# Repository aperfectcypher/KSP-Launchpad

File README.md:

# KSP-Launchpad
## THIS IS AN EARLY WORK IN PROGRESS

Firmware for the KSP-Launchpad board.

MCU is an ATmega2560.
## Features

* Dual 3-axis joystick for rotation and translation
* Linear potentiometers for throttle
* SAS LED
* RCS LED
* LED bars as ship ressources gauges
* LCD screen (128x32px) for ship status

## Schematics

The schematics are written using kicad.
The schematics are available in the `schematics` directory.

## License

The firmware and schematics are licensed under the Unlicense license.

## Author

[Aperfectcypher](https://github.com/aperfectcypher)

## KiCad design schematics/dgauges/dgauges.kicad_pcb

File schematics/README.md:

# Schematics
The schematics are written using kicad.

Required libraries:
* [Connectors_JST](https://github.com/KiCad/Connectors_JST.pretty)

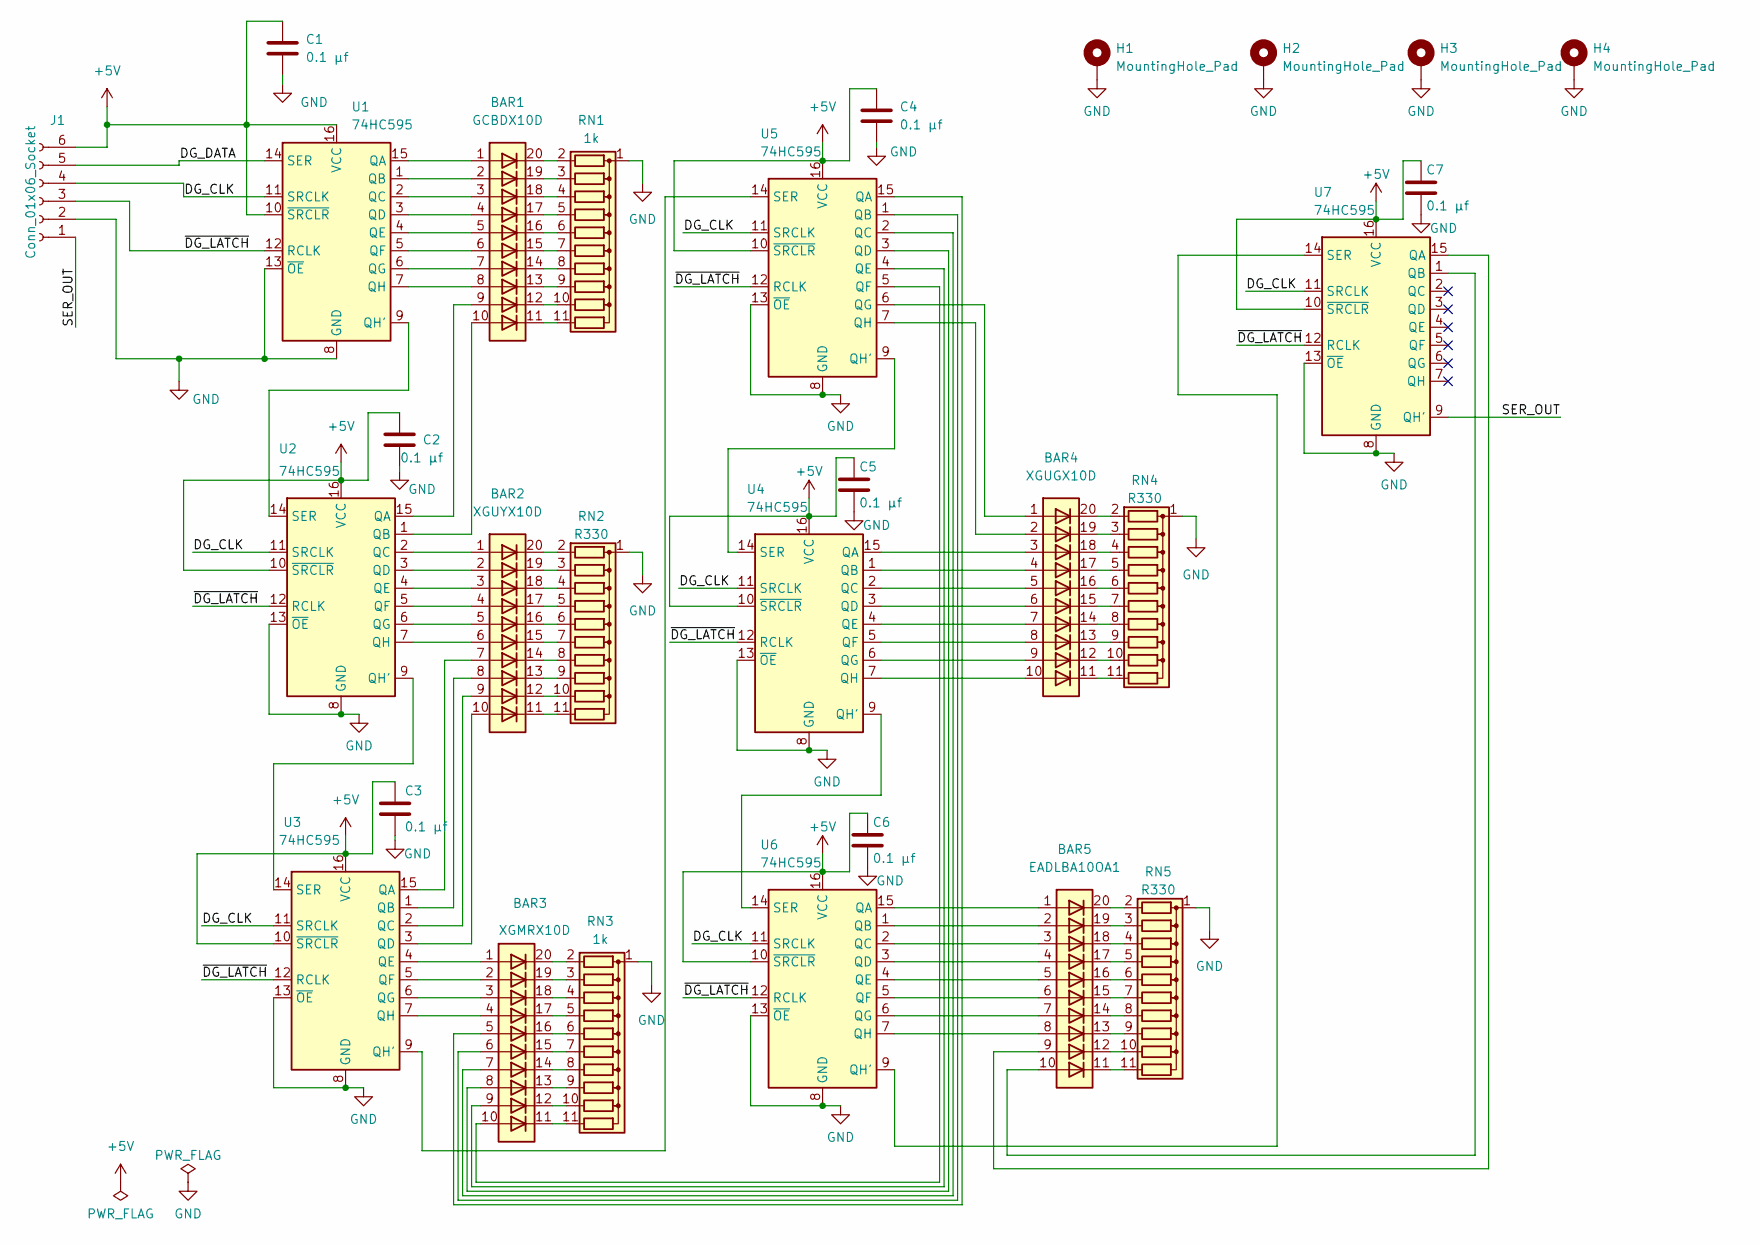
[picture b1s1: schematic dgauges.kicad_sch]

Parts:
BAR1: GCBDX10D; HDSP-4832
BAR2: XGUYX10D; HDSP-4832
BAR3: XGMRX10D; HDSP-4832
BAR4: XGUGX10D; HDSP-4832
BAR5: EADLBA10OA1; HDSP-4832
C1, C2, C3, C4, C5, C6, C7: 0.1 µf; C_Disc_D4.3mm_W1.9mm_P5.00mm; LCSC C254085
H1, H2, H3, H4: MountingHole_Pad; MountingHole_2.2mm_M2_ISO7380_Pad
J1: Conn_01x06_Socket; JST_PH_B6B-PH-K_1x06_P2.00mm_Vertical
RN1, RN3: 1k; R_Array_SIP11; digikey 4611X-101-102LF-ND
RN2, RN4, RN5: R330; R_Array_SIP11; digi-key 4611X-101-331LF
U1, U2, U3, U4, U5, U6, U7: 74HC595; DIP-16_W7.62mm

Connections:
+5V: C1.1, C2.1, C3.1, C4.1, C5.1, C6.1, C7.1, J1.6, U1.10 (~SRCLR), U1.16 (VCC), U2.10 (~SRCLR), U2.16 (VCC), U3.10 (~SRCLR), U3.16 (VCC), U4.10 (~SRCLR), U4.16 (VCC), U5.10 (~SRCLR), U5.16 (VCC), U6.10 (~SRCLR), U6.16 (VCC), U7.10 (~SRCLR), U7.16 (VCC)
/DG_CLK: J1.4, U1.11 (SRCLK), U2.11 (SRCLK), U3.11 (SRCLK), U4.11 (SRCLK), U5.11 (SRCLK), U6.11 (SRCLK), U7.11 (SRCLK)
/DG_DATA: J1.5, U1.14 (SER)
/SER_OUT: J1.1, U7.9 (QH')
/~DG_LATCH: J1.3, U1.12 (RCLK), U2.12 (RCLK), U3.12 (RCLK), U4.12 (RCLK), U5.12 (RCLK), U6.12 (RCLK), U7.12 (RCLK)
GND: C1.2, C2.2, C3.2, C4.2, C5.2, C6.2, C7.2, H1.1, H2.1, H3.1, H4.1, J1.2, RN1.1 (common), RN2.1 (common), RN3.1 (common), RN4.1 (common), RN5.1 (common), U1.8 (GND), U1.13 (~OE), U2.8 (GND), U2.13 (~OE), U3.8 (GND), U3.13 (~OE), U4.8 (GND), U4.13 (~OE), U5.8 (GND), U5.13 (~OE), U6.8 (GND), U6.13 (~OE), U7.8 (GND), U7.13 (~OE)
unnamed: BAR1.20 (K), RN1.2 (R1)
unnamed: BAR1.19 (K), RN1.3 (R2)
unnamed: BAR1.18 (K), RN1.4 (R3)
unnamed: BAR1.17 (K), RN1.5 (R4)
unnamed: BAR1.16 (K), RN1.6 (R5)
unnamed: BAR1.15 (K), RN1.7 (R6)
unnamed: BAR1.14 (K), RN1.8 (R7)
unnamed: BAR1.13 (K), RN1.9 (R8)
unnamed: BAR1.12 (K), RN1.10 (R9)
unnamed: BAR1.11 (K), RN1.11 (R10)
unnamed: BAR2.20 (K), RN2.2 (R1)
unnamed: BAR2.19 (K), RN2.3 (R2)
unnamed: BAR2.18 (K), RN2.4 (R3)
unnamed: BAR2.17 (K), RN2.5 (R4)
unnamed: BAR2.16 (K), RN2.6 (R5)
unnamed: BAR2.15 (K), RN2.7 (R6)
unnamed: BAR2.14 (K), RN2.8 (R7)
unnamed: BAR2.13 (K), RN2.9 (R8)
unnamed: BAR2.12 (K), RN2.10 (R9)
unnamed: BAR2.11 (K), RN2.11 (R10)
unnamed: BAR3.20 (K), RN3.2 (R1)
unnamed: BAR3.19 (K), RN3.3 (R2)
unnamed: BAR3.18 (K), RN3.4 (R3)
unnamed: BAR3.17 (K), RN3.5 (R4)
unnamed: BAR3.16 (K), RN3.6 (R5)
unnamed: BAR3.15 (K), RN3.7 (R6)
unnamed: BAR3.14 (K), RN3.8 (R7)
unnamed: BAR3.13 (K), RN3.9 (R8)
unnamed: BAR3.12 (K), RN3.10 (R9)
unnamed: BAR3.11 (K), RN3.11 (R10)
unnamed: BAR4.20 (K), RN4.2 (R1)
unnamed: BAR4.19 (K), RN4.3 (R2)
unnamed: BAR4.18 (K), RN4.4 (R3)
unnamed: BAR4.17 (K), RN4.5 (R4)
unnamed: BAR4.16 (K), RN4.6 (R5)
unnamed: BAR4.15 (K), RN4.7 (R6)
unnamed: BAR4.14 (K), RN4.8 (R7)
unnamed: BAR4.13 (K), RN4.9 (R8)
unnamed: BAR4.12 (K), RN4.10 (R9)
unnamed: BAR4.11 (K), RN4.11 (R10)
unnamed: BAR5.20 (K), RN5.2 (R1)
unnamed: BAR5.19 (K), RN5.3 (R2)
unnamed: BAR5.18 (K), RN5.4 (R3)
unnamed: BAR5.17 (K), RN5.5 (R4)
unnamed: BAR5.16 (K), RN5.6 (R5)
unnamed: BAR5.15 (K), RN5.7 (R6)
unnamed: BAR5.14 (K), RN5.8 (R7)
unnamed: BAR5.13 (K), RN5.9 (R8)
unnamed: BAR5.12 (K), RN5.10 (R9)
unnamed: BAR5.11 (K), RN5.11 (R10)
unnamed: BAR1.1 (A), U1.15 (QA)
unnamed: BAR1.2 (A), U1.1 (QB)
unnamed: BAR1.3 (A), U1.2 (QC)
unnamed: BAR1.4 (A), U1.3 (QD)
unnamed: BAR1.5 (A), U1.4 (QE)
unnamed: BAR1.6 (A), U1.5 (QF)
unnamed: BAR1.7 (A), U1.6 (QG)
unnamed: U1.9 (QH'), U2.14 (SER)
unnamed: BAR1.8 (A), U1.7 (QH)
unnamed: BAR1.9 (A), U2.15 (QA)
unnamed: BAR1.10 (A), U2.1 (QB)
unnamed: BAR2.1 (A), U2.2 (QC)
unnamed: BAR2.2 (A), U2.3 (QD)
unnamed: BAR2.3 (A), U2.4 (QE)
unnamed: BAR2.4 (A), U2.5 (QF)
unnamed: BAR2.5 (A), U2.6 (QG)
unnamed: U2.9 (QH'), U3.14 (SER)
unnamed: BAR2.6 (A), U2.7 (QH)
unnamed: BAR2.7 (A), U3.15 (QA)
unnamed: BAR2.8 (A), U3.1 (QB)
unnamed: BAR2.9 (A), U3.2 (QC)
unnamed: BAR2.10 (A), U3.3 (QD)
unnamed: BAR3.1 (A), U3.4 (QE)
unnamed: BAR3.2 (A), U3.5 (QF)
unnamed: BAR3.3 (A), U3.6 (QG)
unnamed: U3.9 (QH'), U5.14 (SER)
unnamed: BAR3.4 (A), U3.7 (QH)
unnamed: BAR4.3 (A), U4.15 (QA)
unnamed: BAR4.4 (A), U4.1 (QB)
unnamed: BAR4.5 (A), U4.2 (QC)
unnamed: BAR4.6 (A), U4.3 (QD)
unnamed: BAR4.7 (A), U4.4 (QE)
unnamed: BAR4.8 (A), U4.5 (QF)
unnamed: BAR4.9 (A), U4.6 (QG)
unnamed: U4.9 (QH'), U6.14 (SER)
unnamed: BAR4.10 (A), U4.7 (QH)
unnamed: U4.14 (SER), U5.9 (QH')
unnamed: BAR3.5 (A), U5.15 (QA)
unnamed: BAR3.6 (A), U5.1 (QB)
unnamed: BAR3.7 (A), U5.2 (QC)
unnamed: BAR3.8 (A), U5.3 (QD)
unnamed: BAR3.9 (A), U5.4 (QE)
unnamed: BAR3.10 (A), U5.5 (QF)
unnamed: BAR4.1 (A), U5.6 (QG)
unnamed: BAR4.2 (A), U5.7 (QH)
unnamed: BAR5.1 (A), U6.15 (QA)
unnamed: BAR5.2 (A), U6.1 (QB)
unnamed: BAR5.3 (A), U6.2 (QC)
unnamed: BAR5.4 (A), U6.3 (QD)
unnamed: BAR5.5 (A), U6.4 (QE)
unnamed: BAR5.6 (A), U6.5 (QF)
unnamed: BAR5.7 (A), U6.6 (QG)
unnamed: U6.9 (QH'), U7.14 (SER)
unnamed: BAR5.8 (A), U6.7 (QH)
unnamed: BAR5.9 (A), U7.15 (QA)
unnamed: BAR5.10 (A), U7.1 (QB)

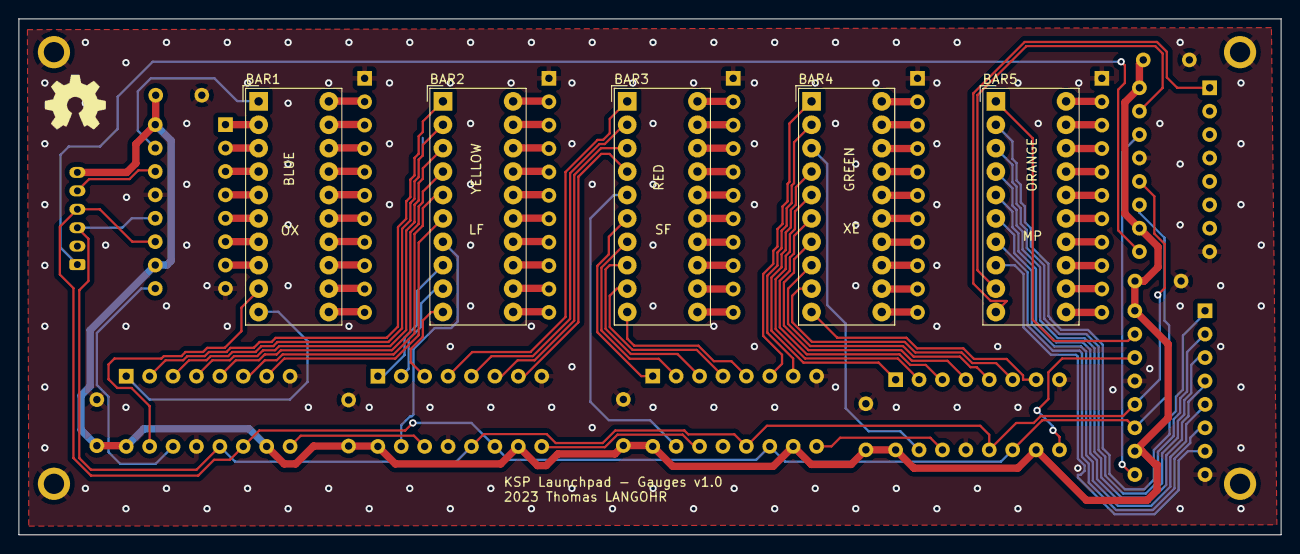
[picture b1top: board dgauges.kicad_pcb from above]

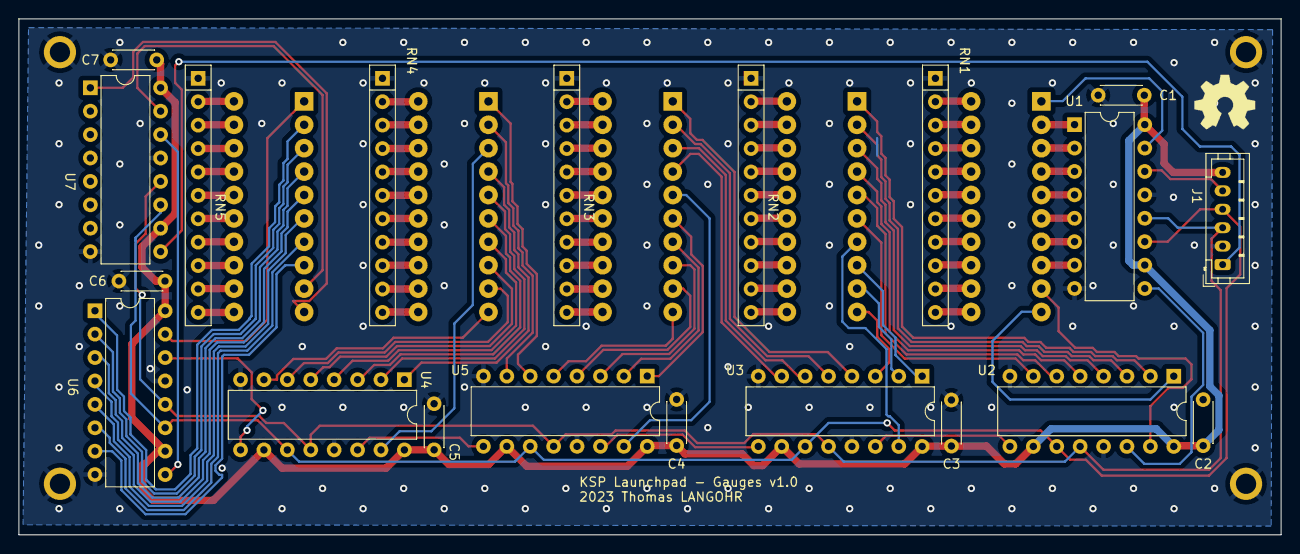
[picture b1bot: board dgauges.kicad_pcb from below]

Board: 2 copper layers, 137.0 x 56.0 mm, 29 parts (20 on the bottom side), 112 nets.

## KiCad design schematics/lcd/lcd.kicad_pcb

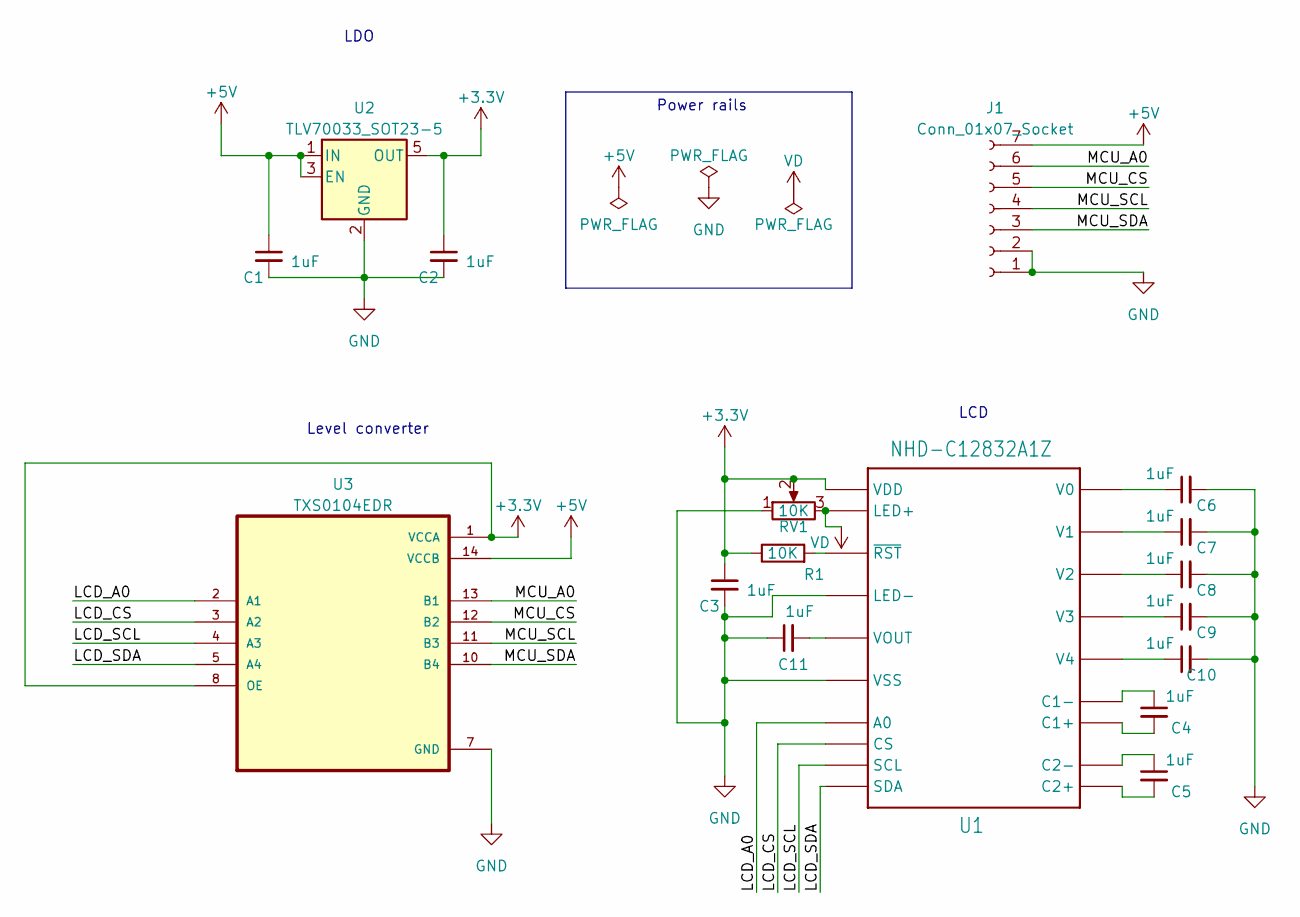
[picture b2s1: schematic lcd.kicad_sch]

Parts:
C1, C2, C3, C4, C5, C6, C7, C8, C9, C10, C11: 1uF; C_0603_1608Metric; lcsc C59302
J1: Conn_01x07_Socket; JST_PH_B7B-PH-K_1x07_P2.00mm_Vertical
R1: 10K; R_0603_1608Metric; lcsc C25804
RV1: 10K; Potentiometer_Bourns_3314G_Vertical; lcsc C780220
U1: NHD-C12832A1Z; JLCPCB BOM 0
U2: TLV70033_SOT23-5; SOT-23-5
U3: TXS0104EDR; SOIC127P600X175-14N; LCSC C79342

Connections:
+3.3V: C2.1, C3.1, R1.1, RV1.2, U1.P12 (VDD), U2.5 (OUT), U3.1 (VCCA), U3.8 (OE)
+5V: C1.1, J1.7, U2.1 (IN), U2.3 (EN), U3.14 (VCCB)
/LCD_A0: U1.P15 (A0), U3.2 (A1)
/LCD_CS: U1.P17 (CS), U3.3 (A2)
/LCD_SCL: U1.P14 (SCL), U3.4 (A3)
/LCD_SDA: U1.P13 (SDA), U3.5 (A4)
/MCU_A0: J1.6, U3.13 (B1)
/MCU_CS: J1.5, U3.12 (B2)
/MCU_SCL: J1.4, U3.11 (B3)
/MCU_SDA: J1.3, U3.10 (B4)
GND: C1.2, C2.2, C3.2, C6.2, C7.2, C8.2, C9.2, C10.2, C11.1, J1.1, J1.2, RV1.1, U1.P11 (VSS), U1.P19 (LED-), U2.2 (GND), U3.7 (GND)
unnamed: C4.2, U1.P8 (C1+)
unnamed: C4.1, U1.P9 (C1-)
unnamed: C5.2, U1.P7 (C2+)
unnamed: C5.1, U1.P6 (C2-)
unnamed: C6.1, U1.P1 (V0)
unnamed: C7.1, U1.P2 (V1)
unnamed: C8.1, U1.P3 (V2)
unnamed: C9.1, U1.P4 (V3)
unnamed: C10.1, U1.P5 (V4)
unnamed: C11.2, U1.P10 (VOUT)
unnamed: R1.2, U1.P16 (~RST)
VD: RV1.3, U1.P18 (LED+)

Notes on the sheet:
LCD
Level converter
Power rails
LDO

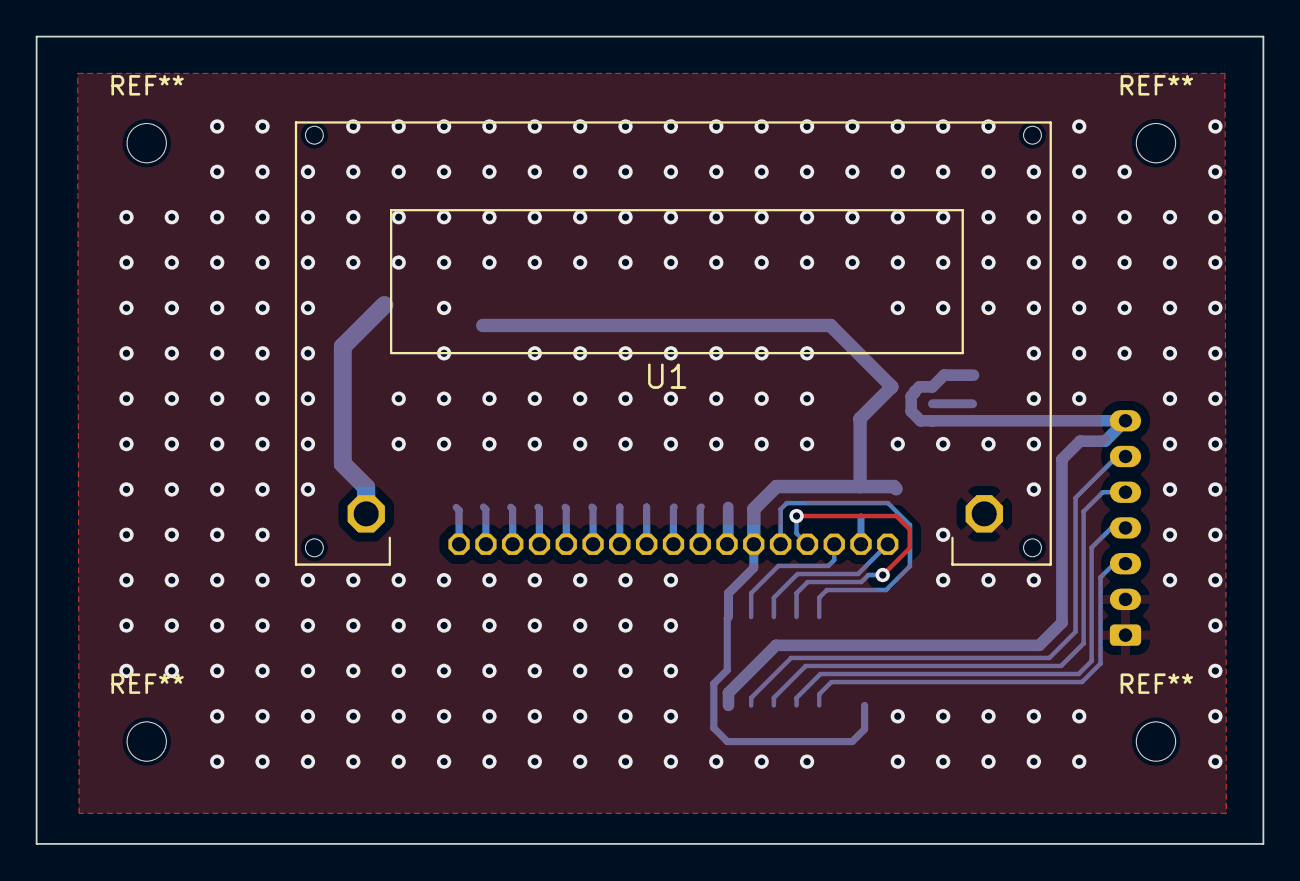
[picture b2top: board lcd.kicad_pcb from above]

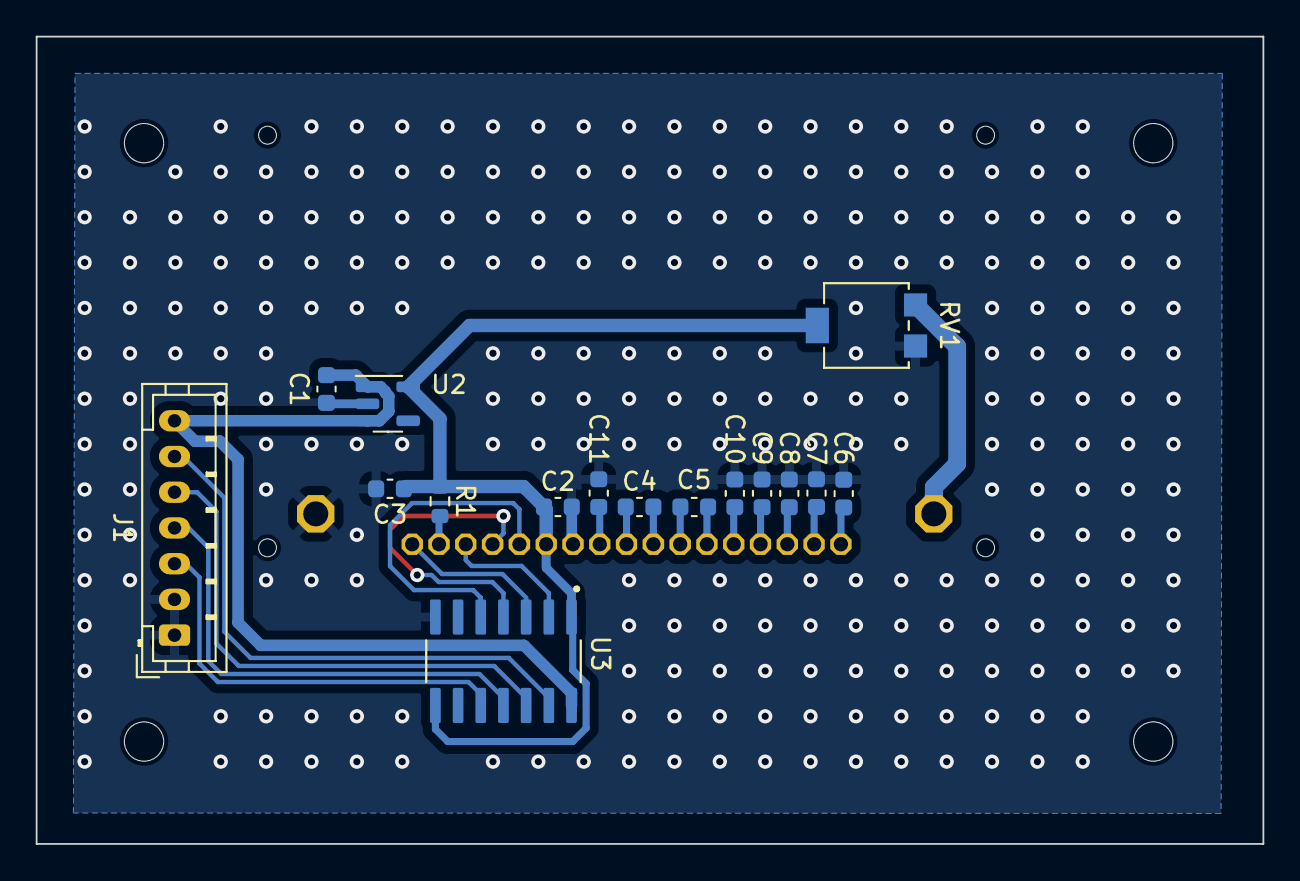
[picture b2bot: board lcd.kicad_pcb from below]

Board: 2 copper layers, 68.7 x 45.2 mm, 17 parts (16 on the bottom side), 23 nets.

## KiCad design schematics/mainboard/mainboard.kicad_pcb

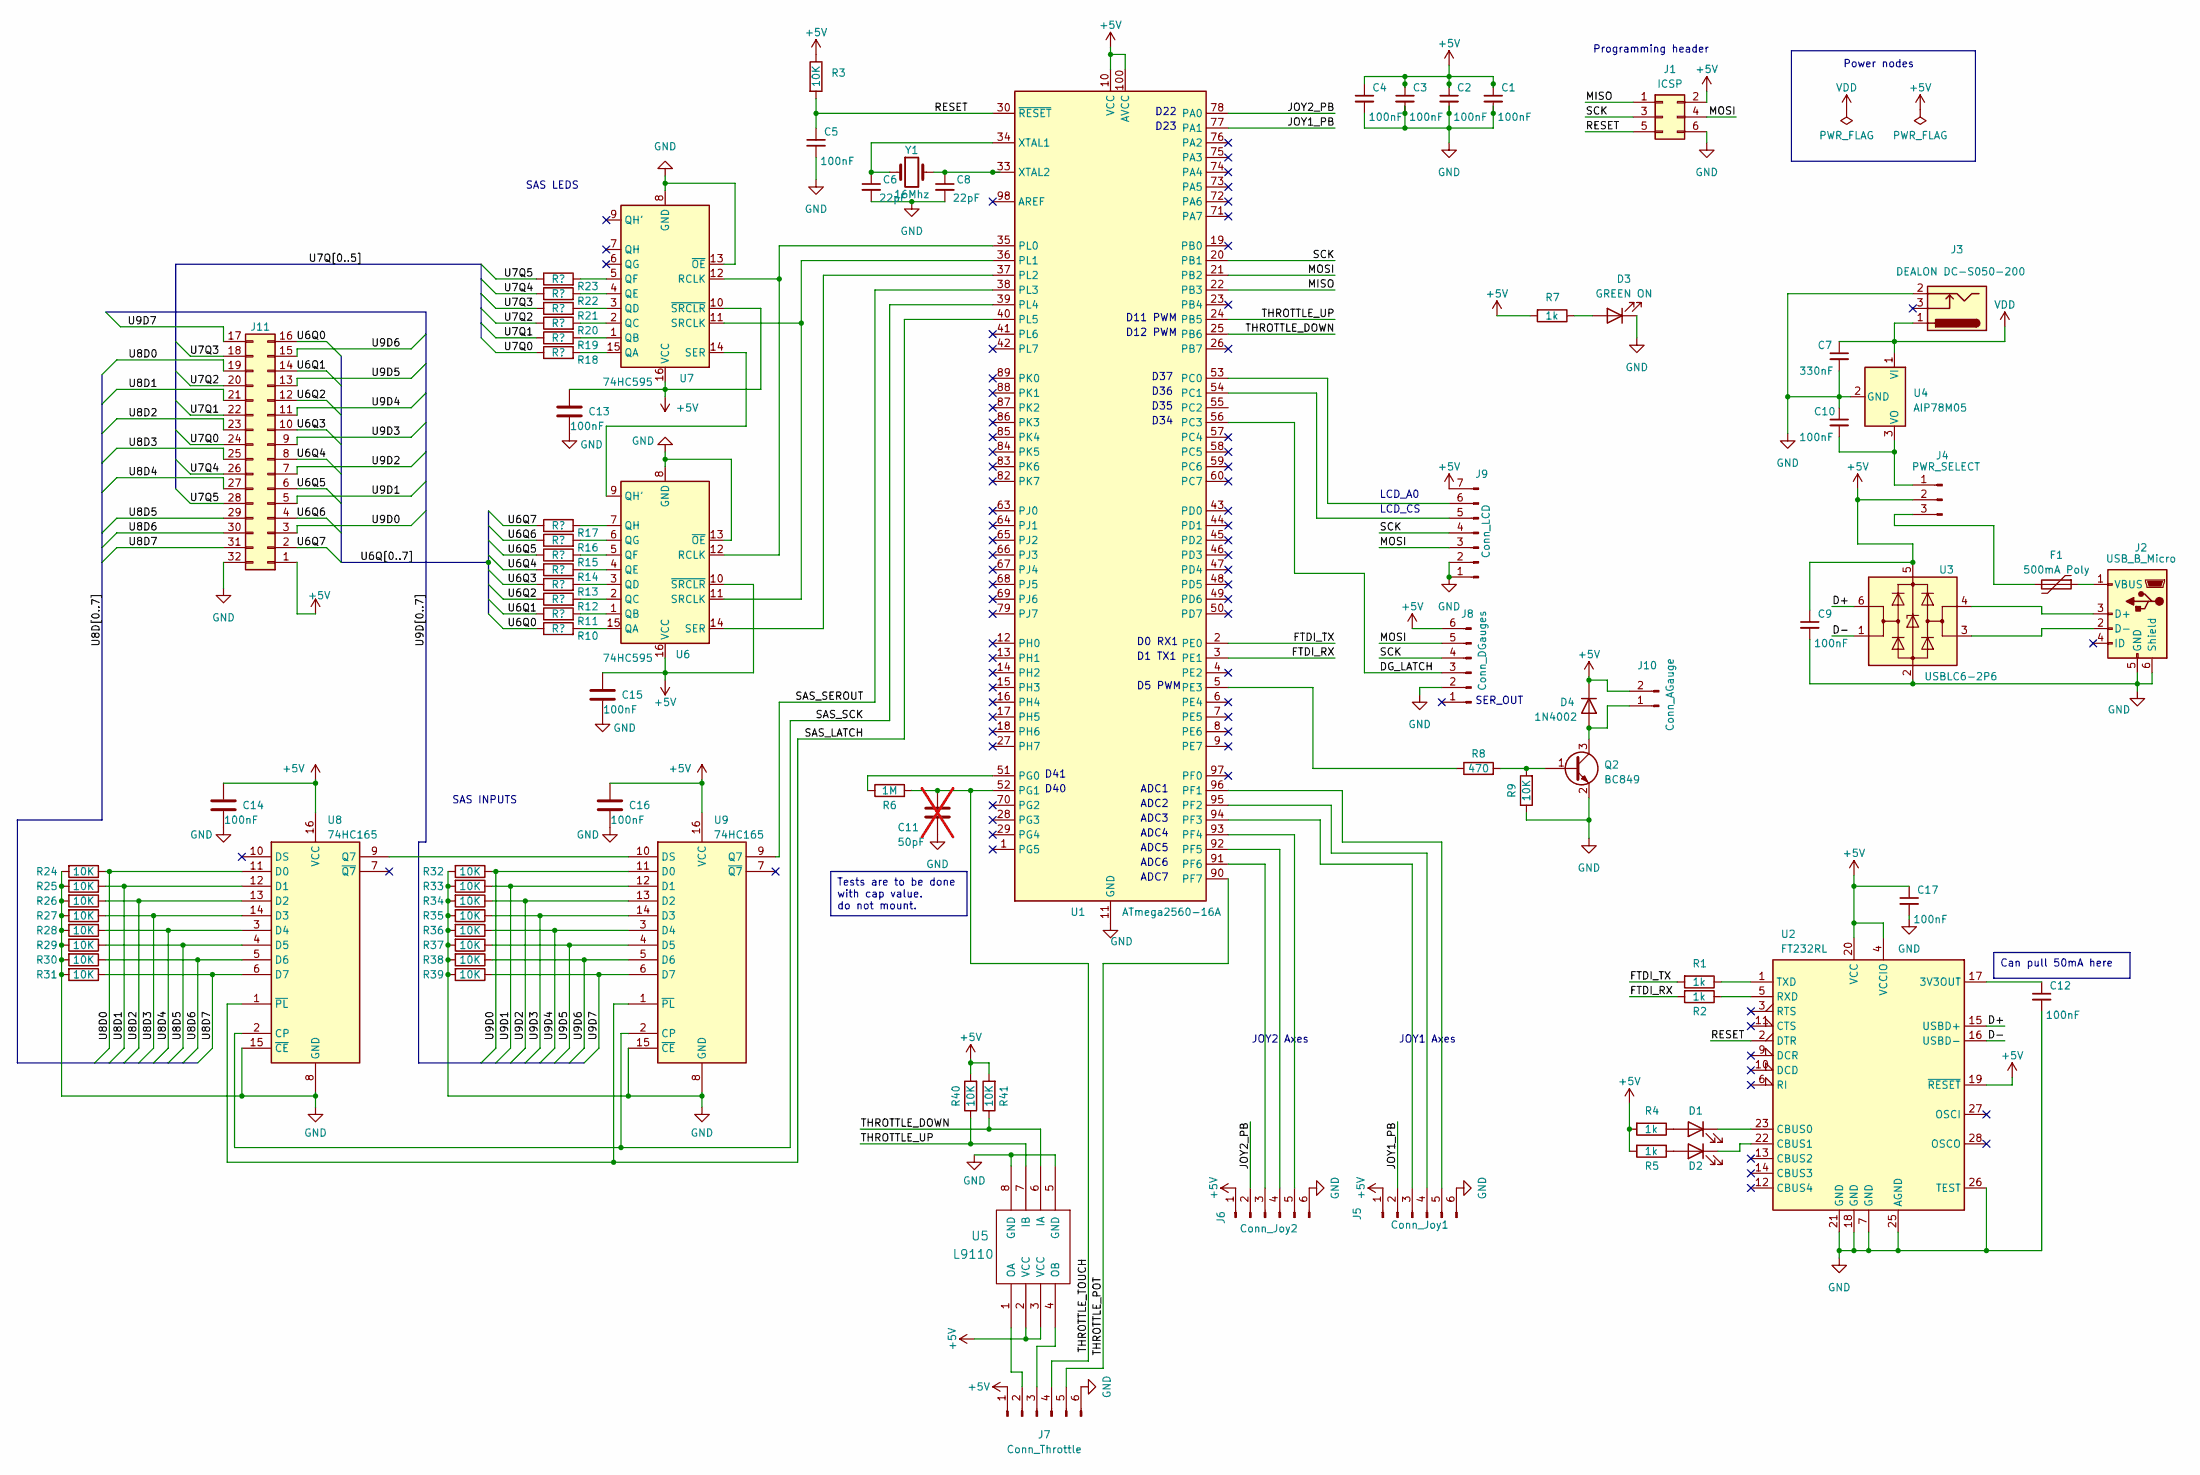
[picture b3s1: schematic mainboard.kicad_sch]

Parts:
C1, C2, C3, C4, C5, C9, C12, C17: 100nF; C_0603_1608Metric; lcsc C30926
C6, C8: 22pF; C_0603_1608Metric; lcsc C105620
C7: 330nF; C_0603_1608Metric; lcsc C282682
C10: 100nF; C_0603_1608Metric; lcsc C14665
C11: 50pF; C_0603_1608Metric; not fitted
C13, C14, C15, C16: 100nF; C_0603_1608Metric
D1, D2: LED; LED_1206_3216Metric
D3: GREEN ON; LED_0603_1608Metric
D4: 1N4002; D_SOD-123F; lcsc C169542
F1: 500mA Poly; Fuse_0603_1608Metric; lcsc C311055
J1: ICSP; PinHeader_2x03_P2.54mm_Vertical
J2: USB_B_Micro; USB_Micro-B_Molex-105017-0001; lcsc C962222
J3: DEALON DC-S050-200; BarrelJack_CLIFF_FC681465S_SMT_Horizontal; lcsc C2936010
J4: PWR_SELECT; PinHeader_1x03_P2.54mm_Vertical
J5: Conn_Joy1; JST_PH_B6B-PH-K_1x06_P2.00mm_Vertical
J6: Conn_Joy2; JST_PH_B6B-PH-K_1x06_P2.00mm_Vertical
J7: Conn_Throttle; JST_PH_B6B-PH-K_1x06_P2.00mm_Vertical
J8: Conn_DGauges; JST_PH_B6B-PH-K_1x06_P2.00mm_Vertical
J9: Conn_LCD; JST_PH_B7B-PH-K_1x07_P2.00mm_Vertical
J10: Conn_AGauge; JST_PH_B2B-PH-K_1x02_P2.00mm_Vertical
J11: Conn_SAS; JST_PHD_B32B-PHDSS_2x16_P2.00mm_Vertical; lcsc C1121898
Q2: BC849; SOT-23; lcsc C475633
R1, R2, R4, R5, R7: 1k; R_0603_1608Metric; lcsc C21190
R3: 10K; R_0603_1608Metric; lcsc C25804
R6: 1M; R_0603_1608Metric
R8: 470; R_0603_1608Metric
R9, R24, R25, R26, R27, R28, R29, R30, R31, R32, R33, R34, R35, R36, R37, R38, R39, R40, R41: 10K; R_0603_1608Metric
R10, R11, R12, R13, R14, R15, R16, R17, R18, R19, R20, R21, R22, R23: R?; R_0603_1608Metric
U1: ATmega2560-16A; TQFP-100_14x14mm_P0.5mm; lcsc C22460
U2: FT232RL; SSOP-28_3.9x9.9mm_P0.635mm
U3: USBLC6-2P6; SOT-666; lcsc C15999
U4: AIP78M05; TO-252-2; lcsc C3019178
U5: L9110; DIP-8_W7.62mm_Socket
U6, U7: 74HC595; DIP-16_W7.62mm
U8, U9: 74HC165; DIP-16_W7.62mm
Y1: 16Mhz; Crystal_SMD_5032-2Pin_5.0x3.2mm; lcsc C112572

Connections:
+5V: C1.1, C2.1, C3.1, C4.1, C9.1, C13.1, C14.1, C15.1, C16.1, C17.1, D4.1 (K), J1.2, J4.2, J5.1, J6.1, J7.1, J8.6, J9.7, J10.2, J11.1, R3.1, R4.2, R5.2, R7.2, R40.2, R41.2, U1.10 (VCC), U1.31 (VCC), U1.61 (VCC), U1.80 (VCC), U1.100 (AVCC), U2.4 (VCCIO), U2.19 (~RESET), U2.20 (VCC), U3.5 (VBUS), U5.2 (VCC), U5.3 (VCC), U6.10 (~SRCLR), U6.16 (VCC), U7.10 (~SRCLR), U7.16 (VCC), U8.16 (VCC), U9.16 (VCC)
/D+: U2.15 (USBD+), U3.6 (I/O1)
/D-: U2.16 (USBD-), U3.1 (I/O1)
/DG_LATCH: J8.3, U1.56 (PC3)
/FTDI_RX: R2.2, U1.3 (PE1)
/FTDI_TX: R1.2, U1.2 (PE0)
/JOY1_PB: J5.2, U1.77 (PA1)
/JOY2_PB: J6.2, U1.78 (PA0)
/MISO: J1.1, U1.22 (PB3)
/MOSI: J1.4, J8.5, J9.3, U1.21 (PB2)
/RESET: C5.1, J1.5, R3.2, U1.30 (~RESET), U2.2 (DTR)
/SAS_LATCH: U1.40 (PL5), U8.1 (~PL), U9.1 (~PL)
/SAS_SCK: U1.39 (PL4), U8.2 (CP), U9.2 (CP)
/SAS_SEROUT: U1.38 (PL3), U9.9 (Q7)
/SCK: J1.3, J8.4, J9.4, U1.20 (PB1)
/THROTTLE_DOWN: R41.1, U1.25 (PB6), U5.6 (IA)
/THROTTLE_POT: J7.5, U1.90 (PF7)
/THROTTLE_TOUCH: C11.1, J7.4, R6.2, U1.52 (PG1)
/THROTTLE_UP: R40.1, U1.24 (PB5), U5.7 (IB)
/U6Q0: J11.16, R10.1
/U6Q1: J11.14, R11.1
/U6Q2: J11.12, R12.1
/U6Q3: J11.10, R13.1
/U6Q4: J11.8, R14.1
/U6Q5: J11.6, R15.1
/U6Q6: J11.4, R16.1
/U6Q7: J11.2, R17.1
/U7Q0: J11.24, R18.1
/U7Q1: J11.22, R19.1
/U7Q2: J11.20, R20.1
/U7Q3: J11.18, R21.1
/U7Q4: J11.26, R22.1
/U7Q5: J11.28, R23.1
/U8D0: J11.19, R24.1, U8.11 (D0)
/U8D1: J11.21, R25.1, U8.12 (D1)
/U8D2: J11.23, R26.1, U8.13 (D2)
/U8D3: J11.25, R27.1, U8.14 (D3)
/U8D4: J11.27, R28.1, U8.3 (D4)
/U8D5: J11.29, R29.1, U8.4 (D5)
/U8D6: J11.30, R30.1, U8.5 (D6)
/U8D7: J11.31, R31.1, U8.6 (D7)
/U9D0: J11.3, R32.1, U9.11 (D0)
/U9D1: J11.5, R33.1, U9.12 (D1)
/U9D2: J11.7, R34.1, U9.13 (D2)
/U9D3: J11.9, R35.1, U9.14 (D3)
/U9D4: J11.11, R36.1, U9.3 (D4)
/U9D5: J11.13, R37.1, U9.4 (D5)
/U9D6: J11.15, R38.1, U9.5 (D6)
/U9D7: J11.17, R39.1, U9.6 (D7)
GND: C1.2, C2.2, C3.2, C4.2, C5.2, C6.2, C7.2, C8.2, C9.2, C10.1, C11.2, C12.2, C13.2, C14.2, C15.2, C16.2, C17.2, D3.1 (K), J1.6, J2.5 (GND), J2.6 (Shield), J3.2, J5.6, J6.6, J7.6, J8.2, J9.1, J9.2, J11.32, Q2.2 (E), R9.1, R24.2, R25.2, R26.2, R27.2, R28.2, R29.2, R30.2, R31.2, R32.2, R33.2, R34.2, R35.2, R36.2, R37.2, R38.2, R39.2, U1.11 (GND), U1.32 (GND), U1.62 (GND), U1.81 (GND), U1.99 (GND), U2.7 (GND), U2.18 (GND), U2.21 (GND), U2.25 (AGND), U2.26 (TEST), U3.2 (GND), U4.2 (GND), U5.5 (GND), U5.8 (GND), U6.8 (GND), U6.13 (~OE), U7.8 (GND), U7.13 (~OE), U8.8 (GND), U8.15 (~CE), U9.8 (GND), U9.15 (~CE)
unnamed: D1.2 (A), R4.1
unnamed: D1.1 (K), U2.23 (CBUS0)
unnamed: D2.2 (A), R5.1
unnamed: D2.1 (K), U2.22 (CBUS1)
unnamed: D3.2 (A), R7.1
unnamed: D4.2 (A), J10.1, Q2.3 (C)
unnamed: J2.3 (D+), U3.4 (I/O2)
unnamed: J2.2 (D-), U3.3 (I/O2)
unnamed: F1.1, J2.1 (VBUS)
unnamed: C10.2, J4.1, U4.3 (VO)
unnamed: F1.2, J4.3
unnamed: J5.3, U1.94 (PF3)
unnamed: J5.4, U1.95 (PF2)
unnamed: J5.5, U1.96 (PF1)
unnamed: J6.3, U1.91 (PF6)
unnamed: J6.4, U1.92 (PF5)
unnamed: J6.5, U1.93 (PF4)
unnamed: J7.2, U5.1 (OA)
unnamed: J7.3, U5.4 (OB)
unnamed: J9.5, U1.54 (PC1)
unnamed: J9.6, U1.53 (PC0)
unnamed: Q2.1 (B), R8.2, R9.2
unnamed: R8.1, U1.5 (PE3)
unnamed: R6.1, U1.51 (PG0)
unnamed: U1.35 (PL0), U6.12 (RCLK), U7.12 (RCLK)
unnamed: U1.36 (PL1), U6.11 (SRCLK), U7.11 (SRCLK)
unnamed: U1.37 (PL2), U6.14 (SER)
unnamed: C6.1, U1.34 (XTAL1), Y1.1
unnamed: C8.1, U1.33 (XTAL2), Y1.2
unnamed: C12.1, U2.17 (3V3OUT)
unnamed: R2.1, U2.5 (RXD)
unnamed: R1.1, U2.1 (TXD)
unnamed: R10.2, U6.15 (QA)
unnamed: R11.2, U6.1 (QB)
unnamed: R12.2, U6.2 (QC)
unnamed: R13.2, U6.3 (QD)
unnamed: R14.2, U6.4 (QE)
unnamed: R15.2, U6.5 (QF)
unnamed: R16.2, U6.6 (QG)
unnamed: U6.9 (QH'), U7.14 (SER)
unnamed: R17.2, U6.7 (QH)
unnamed: R18.2, U7.15 (QA)
unnamed: R19.2, U7.1 (QB)
unnamed: R20.2, U7.2 (QC)
unnamed: R21.2, U7.3 (QD)
unnamed: R22.2, U7.4 (QE)
unnamed: R23.2, U7.5 (QF)
unnamed: U8.9 (Q7), U9.10 (DS)
VDD: C7.1, J3.1, U4.1 (VI)

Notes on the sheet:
Tests are to be done with cap value. do not mount.
Can pull 50mA here
ADC3
D37
SAS INPUTS
D36
ADC6
D0 RX1
LCD_A0
D12 PWM
D35
D34
D22
ADC2
ADC7
SER_OUT
ADC4
ADC5
LCD_CS
D40
Programming header
D1 TX1
D23
D11 PWM
D41
JOY2 Axes
SAS LEDS
Power nodes
D5 PWM
JOY1 Axes
ADC1

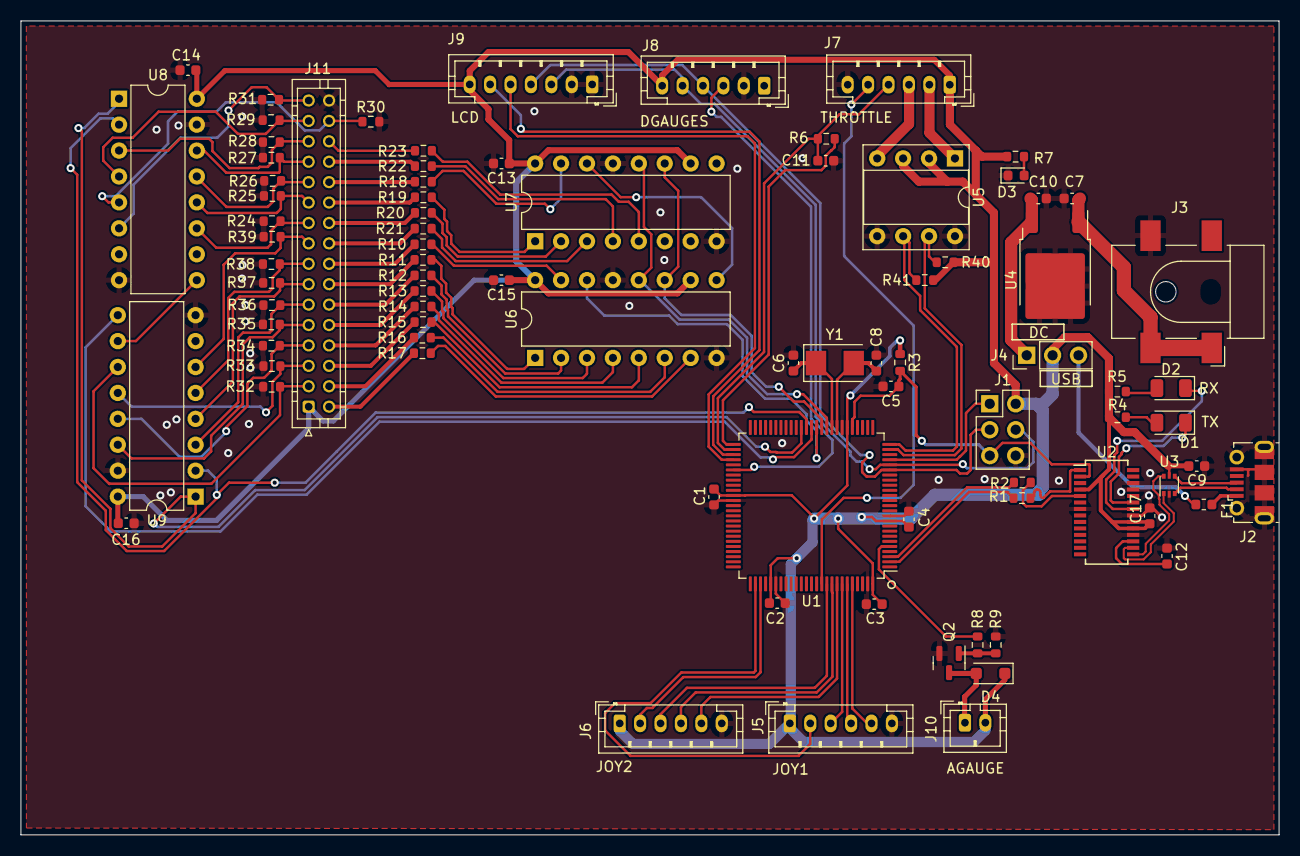
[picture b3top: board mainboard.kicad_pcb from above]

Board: 2 copper layers, 123.3 x 79.8 mm, 85 parts (0 on the bottom side), 99 nets.

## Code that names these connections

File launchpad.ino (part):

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#define THROTTLE_TOUCH_SEND_PIN    51
#define THROTTLE_TOUCH_RECV_PIN    52
/* PLACEHOLDER TODO CORRECT PIN & NAME */
#define pb1                        24
#define pb2                        25

// Joystick 1
#define JOY1_X_PIN         PIN_A1
#define JOY1_Y_PIN         PIN_A2
#define JOY1_Z_PIN         PIN_A3
#define JOY1_PB_PIN        22

// Joystick 2
#define JOY2_X_PIN         PIN_A4
#define JOY2_Y_PIN         PIN_A5
#define JOY2_Z_PIN         PIN_A6
#define JOY2_PB_PIN        23

// Digital gauges
#define DGAUGES_LATCH_PIN  34
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  pinMode(THROTTLE_MOT_REV_PIN, OUTPUT);
  pinMode(THROTTLE_INPUT_PIN, INPUT);
  /* DEBUG TODO RM*/
  pinMode(pb1, INPUT);
  pinMode(pb2, INPUT);

  // Setup SPI for the digital gauges / LCD display
  SPI.begin();
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  simpitClient.send(THROTTLE_MESSAGE, throttleMsg);

  // Throttle motor management
  if (digitalRead(pb1) == HIGH)
  {
    throttle_motorTarget_sw = throttle_sliderMax_w;
  }
  else if (digitalRead(pb2) == HIGH)
  {
    throttle_motorTarget_sw = throttle_sliderMin_w;
  }
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
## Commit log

2023-03-28 initial README and sources
2023-03-28 Rename kspctrl to launchpad
2023-03-28 Fix typo in README.md: "Linaer" to "Linear" for throttle potentiometers
2023-03-28 Initial kicad files (wip)
2023-03-28 Readme for the schematics directory
2023-03-28 Update README.md to clarify the type of MCU used as an ATmega2560
2023-03-28 SCH: Gauges routing complete
2023-03-29 SCH: routing improvement
    +ground plane
    +via stiching
2023-03-29 Ignore new schematics/fab_out/ directory
2023-03-29 SCH: Mainboard wip
2023-03-29 SCH: mv sch to root dir / dgauges: GND plane filling, via stiching
2023-03-30 SCH: dgauge => ust proper JST connector for J1
2023-03-30 Update digital gauges with ship fuel percentage
2023-03-30 Update README.md
    Led gauges
2023-03-30 Update README.md
    Typo
2023-04-03 SCH: DGauges: route serial out to header for daisy-chaining
    And add mounting holes
2023-04-03 add license statement
2023-04-03 SCH: tune mounting holes
2023-04-03 SCH: maionboard base, routing in progress
2023-04-03 SCH: mainboard: cont.
2023-04-04 SCH: mainboard=> +regu on VIN. routing cont.
2023-04-06 SCH: mainboard=> joy2 header + throttle header
2023-04-06 SCH: mainboard=> DGAUGES header
2023-04-06 Testing lcd
2023-04-06 SCH: dgauges=> set res. values to get similar brightness on all bars
2023-04-07 lcd : display apsides / altitudes.
    change mode with pin 2/3
2023-04-07 SCH: LCD
2023-04-07 SCH: LCD=> add pot for backlight brightness
2023-04-12 SCH: LCD=> Changed level shifter
2023-04-12 LCD: optimized/simplified code. Added analog gauge for EC
2023-04-13 Mainboard: tweak pins, routed lcd connector
2023-04-13 Panels: control panel v1
2023-04-13 Panels: control panel v2 + SAS panel v1
2023-04-17 Sch: gauges: add one for xenon
2023-04-17 Panels: rework of ctrl and sas. Add gauges and v1 of executive
2023-04-17 SCH: mainboard missing cap & gnd connections on ft232
2023-04-18 Panels: rounded iner edges for fab
2023-04-22 SCH: Mainboard: add power LED
2023-04-24 SCH: Mainboard=> LED routing (1)
2023-04-25 SCH: Mainboard=> LED/Buttons routing(2)
2023-04-25 Panels: adjusted toggle switches radius from real parts measurements
2023-04-25 SCH: MAinboard=> Clean DRC issues
2023-04-26 SCH: LCD=> fixes, production ready
2023-04-28 SCH:MB=> fixes + gen jlc fab prj
2023-04-28 SCH:MB=> Changed FT232 package
2023-04-28 SCH:MB=> add pull-up to throttle signals
2023-05-01 Sw: Throttle: motorized slider mgmt, capacitive touch safety
2023-05-02 Test sketch for 74hc595 8 digit 7 segments display
2023-05-07 SCH:MB=> moved decoupling caps to each +5V on the ATMega
2023-05-08 Panels: changed height to 100mm, need to align & anotate 7-seg display
2023-05-10 Panels: added M4 mounting holes
2023-05-18 SCH: LCD => removed MB OE connection, now pulled to 3.3, always ON
2023-05-22 panels: gauges=> aligned mounting holes
